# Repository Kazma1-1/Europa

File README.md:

# Europa

## Europa Directory Organization

| Directory             |Relative path                  |Brief Description                |
| :--------------------:|:-----------------------------:|:-------------------------------:|
| Europa	              |/	                            | root/home folder of project     |
| Europa-Firmware       |Europa/Europa-Firmware/        |Board Firmware                   |
| Europa-Hardware       |	Europa/Europa-Hardware/       |	Hardware design of the board    |
| Europa-Manufacturing  |	Europa/Europa-Manufacturing/  |	Schematic, gerbers, CPL, BOM    |
| Europa-Resources      |	Europa/Europa-Resources/      |	Datasheets & reference manuals  |

<tr></tr>

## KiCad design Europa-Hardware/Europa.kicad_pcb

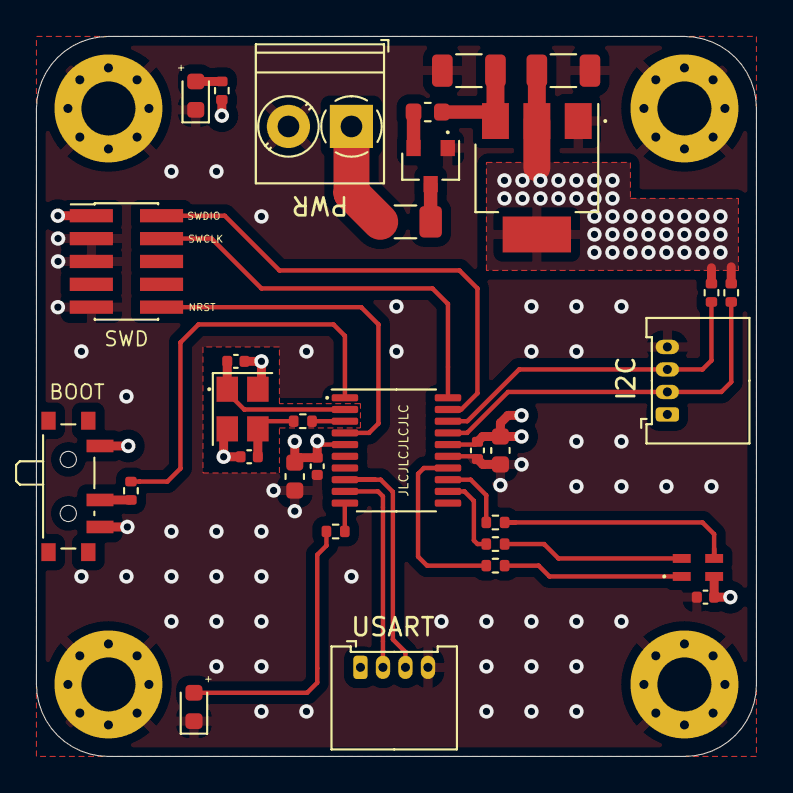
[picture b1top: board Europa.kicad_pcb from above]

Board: 4 copper layers, 40.0 x 40.0 mm, 36 parts (0 on the bottom side), 27 nets.

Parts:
C1: 4u7; C_0603_1608Metric
C2, C6: 100n; C_0402_1005Metric
C3, C4: 6p; C_0402_1005Metric
C5: 1u; C_0603_1608Metric
C7, C8: 10u; C_1206_3216Metric
C12: 10n; C_0402_1005Metric
D3: Green; LED_0603_1608Metric
D4: Yellow; LED_0603_1608Metric
D5: LED_RGBA; WE_WL-SFCD-150066M153000
F1: 1A/33V; Fuse_1206_3216Metric
FB1: 100@100MHz; L_0603_1608Metric
H1, H2, H3, H4: MountingHole_Pad; MountingHole_3mm_Pad_Via
J1: PWR; TerminalBlock_Phoenix_PT-1,5-2-3.5-H_1x02_P3.50mm_Horizontal
J2: I2C1; Molex_PicoBlade_53048-0410_1x04_P1.25mm_Horizontal
J3: SWD; PinHeader_2x05_P1.27mm_Vertical_SMD
J4: USART1; Molex_PicoBlade_53048-0410_1x04_P1.25mm_Horizontal
Q1: AO3401A; SOT-23
R2: 0; R_0402_1005Metric
R3, R6: 4k7; R_0402_1005Metric
R7, R8, R9, R10, R11: 1k5; R_0402_1005Metric
R12: 10k; R_0402_1005Metric
SW1: BOOT; SW_SPDT_PCM12
U1: STM32F030F4Px; TSSOP-20_4.4x6.5mm_P0.65mm
U2: AMS1117-3.3; SOT-223-3_TabPin2
Y1: 16MHz; Crystal_SMD_3225-4Pin_3.2x2.5mm

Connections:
+3V3: C1.1, C2.1, C5.1, C6.1, C8.1, C12.1, D5.4, J2.1, J3.1, J4.1, R3.1, R6.1, R7.2, SW1.1, U1.5, U1.16, U2.2
BOOT: R12.2, U1.1
GND: C1.2, C2.2, C3.1, C4.2, C5.2, C6.2, C7.1, C8.2, C12.2, D3.1, D4.1, H1.1, H2.1, H3.1, H4.1, J1.2, J2.4, J3.3, J3.5, J3.9, J4.4, Q1.1, SW1.3, U1.15, U2.1, Y1.2, Y1.4
I2C1_SCL: J2.2, R3.2, U1.17
I2C1_SDA: J2.3, R6.2, U1.18
NRST: J3.10, U1.4
unnamed: C4.1, R2.2, Y1.3
unnamed: D3.2, R7.1
unnamed: D4.2, R11.1
unnamed: D5.1, R8.1
unnamed: D5.2, R9.1
unnamed: D5.3, R10.1
unnamed: F1.1, Q1.3
unnamed: F1.2, J1.1
unnamed: FB1.2, Q1.2
unnamed: R12.1, SW1.2
RCC_OSC_IN: C3.2, U1.2, Y1.1
RCC_OSC_OUT: R2.1, U1.3
SYS_SWCLK: J3.4, U1.20
SYS_SWDIO: J3.2, U1.19
TIM3_CH1: R9.2, U1.12
TIM3_CH2: R10.2, U1.13
TIM3_CH4: R8.2, U1.14
TIM14_CH1: R11.2, U1.10
USART1_RX: J4.2, U1.9
USART1_TX: J4.3, U1.8
VCC: C7.2, FB1.1, U2.3
